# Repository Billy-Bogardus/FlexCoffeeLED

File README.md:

# FlexCoffeeLED

This Project is for the Flexible Circuit Contest by Hackaday.io
https://hackaday.io/submissions/flexible-circuit-contest/list

The Entry for this Project: https://hackaday.io/project/164555-flexible-coffee-cup-buddy
usefull links:
https://cdn.sparkfun.com/datasheets/BreakoutBoards/WS2812B.pdf

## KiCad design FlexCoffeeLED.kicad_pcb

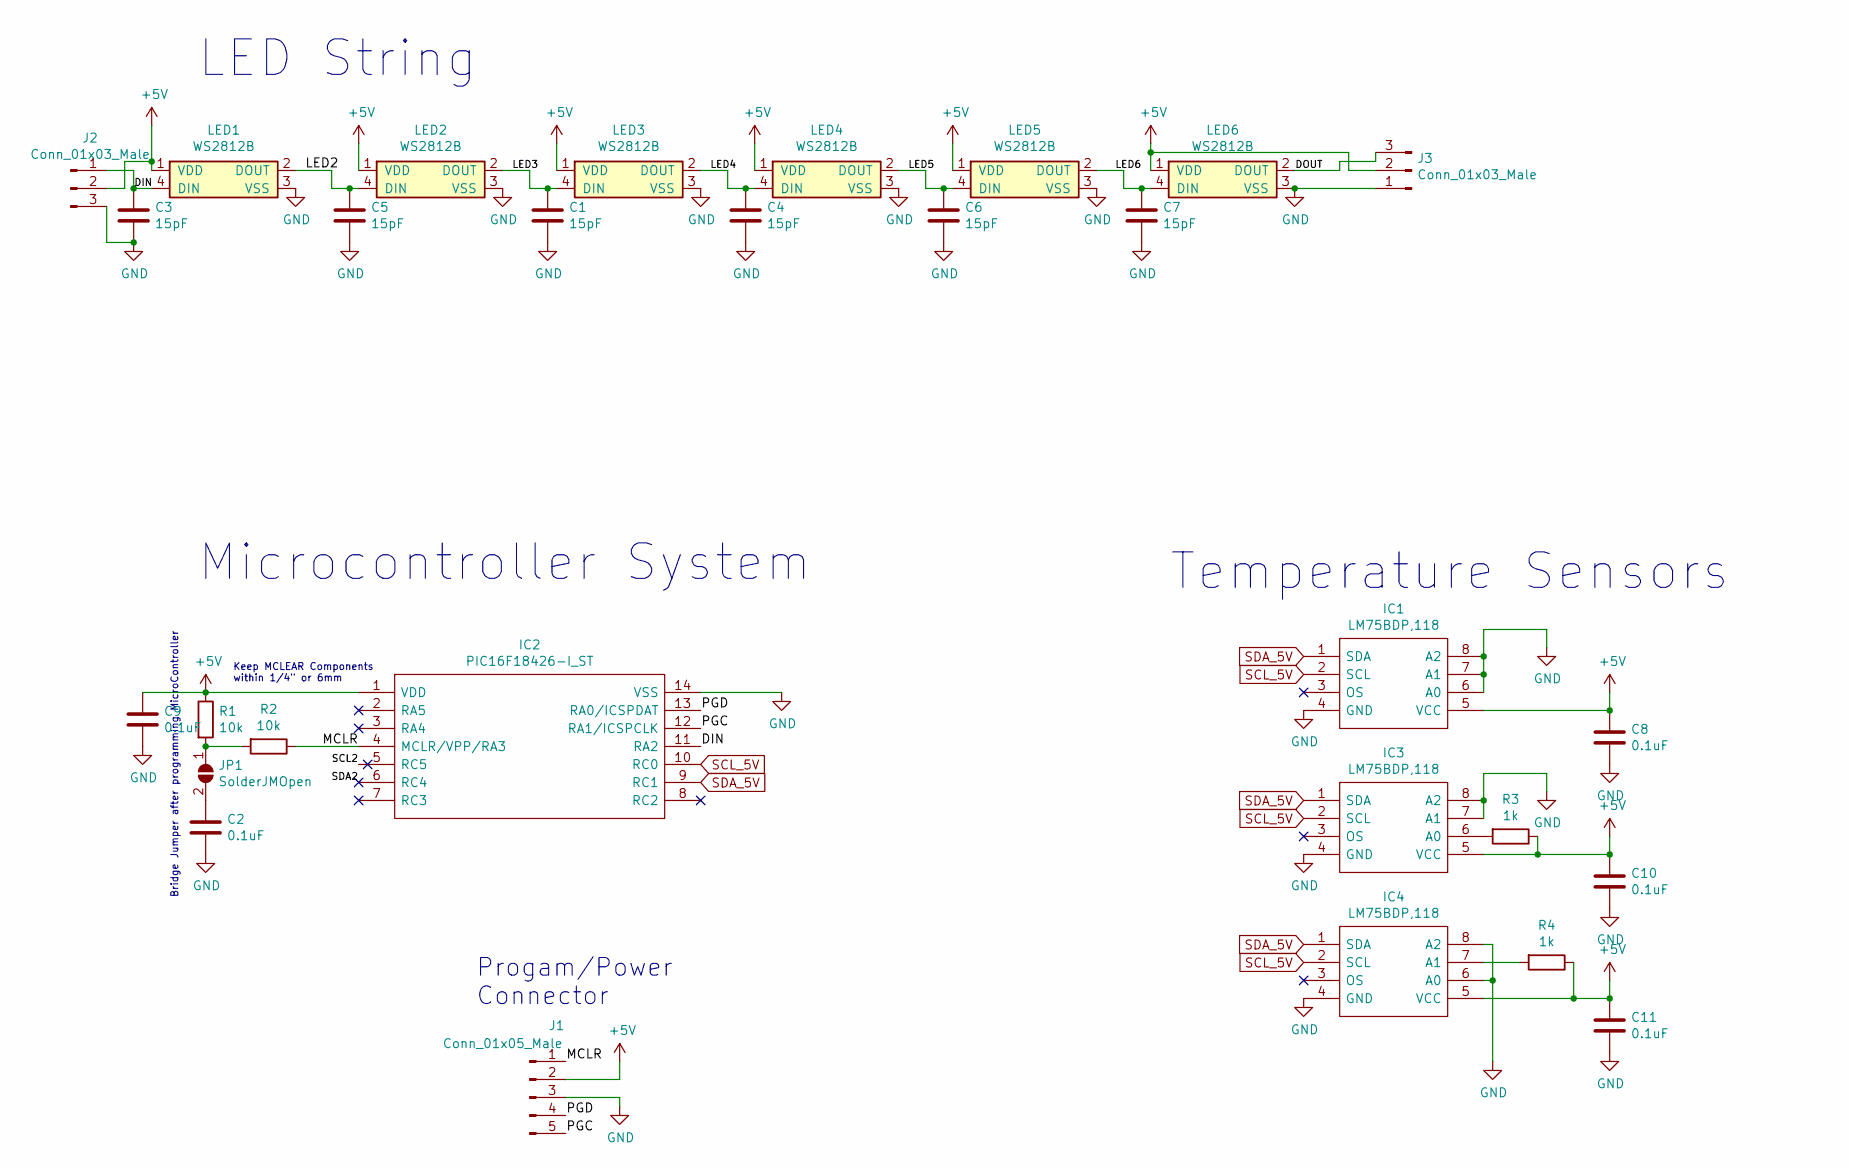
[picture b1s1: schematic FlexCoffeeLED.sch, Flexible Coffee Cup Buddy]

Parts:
C1, C3, C4, C5, C6, C7: 15pF; C_0603
C2, C8, C9, C10, C11: 0.1uF; C_0603
IC1, IC3, IC4: LM75BDP,118; SOP65P490X110-8N; Mouser Part Number 771-LM75BDP
IC2: PIC16F18426-I_ST; SOP65P640X120-14N; Manufacturer_Part_Number PIC16F18426-I/ST
J1: Conn_01x05_Male; Pin_Header_Straight_1x05_Pitch2.54mm
J2, J3: Conn_01x03_Male; Pin_Header_Straight_1x03_Pitch2.54mm
JP1: SolderJMOpen; LED_0603
LED1, LED2, LED3, LED4, LED5, LED6: WS2812B; LED_WS2812B-PLCC4
R1, R2: 10k; R_0603
R3, R4: 1k; R_0603

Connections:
+5V: C8.1, C9.1, C10.1, C11.1, IC1.5 (VCC), IC2.1 (VDD), IC3.5 (VCC), IC4.5 (VCC), J1.2, J2.2, J3.2, LED1.1 (VDD), LED2.1 (VDD), LED3.1 (VDD), LED4.1 (VDD), LED5.1 (VDD), LED6.1 (VDD), R1.1, R3.1, R4.1
/DIN: C3.1, IC2.11 (RA2), J2.1, LED1.4 (DIN)
/DOUT: J3.3, LED6.2 (DOUT)
/LED2: C5.1, LED1.2 (DOUT), LED2.4 (DIN)
/LED3: C1.1, LED2.2 (DOUT), LED3.4 (DIN)
/LED4: C4.1, LED3.2 (DOUT), LED4.4 (DIN)
/LED5: C6.1, LED4.2 (DOUT), LED5.4 (DIN)
/LED6: C7.1, LED5.2 (DOUT), LED6.4 (DIN)
/MCLR: IC2.4 (MCLR/VPP/RA3), J1.1, R2.1
/PGC: IC2.12 (RA1/ICSPCLK), J1.5
/PGD: IC2.13 (RA0/ICSPDAT), J1.4
/SCL2: IC2.5 (RC5)
/SDA2: IC2.6 (RC4)
GND: C1.2, C2.2, C3.2, C4.2, C5.2, C6.2, C7.2, C8.2, C9.2, C10.2, C11.2, IC1.4 (GND), IC1.6 (A0), IC1.7 (A1), IC1.8 (A2), IC2.14 (VSS), IC3.4 (GND), IC3.7 (A1), IC3.8 (A2), IC4.4 (GND), IC4.6 (A0), IC4.8 (A2), J1.3, J2.3, J3.1, LED1.3 (VSS), LED2.3 (VSS), LED3.3 (VSS), LED4.3 (VSS), LED5.3 (VSS), LED6.3 (VSS)
unnamed: C2.1, JP1.2 (B)
unnamed: IC3.6 (A0), R3.2
unnamed: IC4.7 (A1), R4.2
unnamed: JP1.1 (A), R1.2, R2.2
SCL_5V: IC1.2 (SCL), IC2.10 (RC0), IC3.2 (SCL), IC4.2 (SCL)
SDA_5V: IC1.1 (SDA), IC2.9 (RC1), IC3.1 (SDA), IC4.1 (SDA)

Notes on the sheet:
LED String
Microcontroller System
Progam/Power Connector
Bridge Jumper after programming MicroController
Keep MCLEAR Components within 1/4" or 6mm
Temperature Sensors

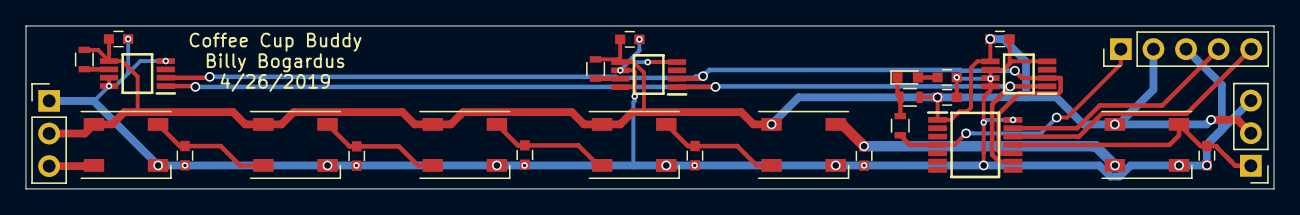
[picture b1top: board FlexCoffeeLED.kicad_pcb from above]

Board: 2 copper layers, 97.3 x 12.7 mm, 29 parts (0 on the bottom side), 18 nets.

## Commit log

2019-04-01 Starting with Clean files after experimenting with GIT.
2019-04-02 Added the major components for the project
2019-04-07 Added Data Sheets Drew Wires and added passive components and connectors
    Changes Committed:
    new file: Datasheet/MCP990_234.pdf
    new file: Datasheet/MCP990_234_AN10.14.pdf
    new file: Datasheet/MCP990_234_AN12.14.pdf
    new file: Datasheet/NCP718-D-1315705.pdf
    new file: Datasheet/Pic18F66k80.pdf
2019-04-07 Add svg diff
2019-04-07 Added Voltage Translator to I2C
2019-04-07 added no connects to up
2019-04-08 Created Board Outlines and Keepouts
2019-04-08 Just Before Renaming Q1 and Q2 Nets
2019-04-08 First Full Routing of Board
2019-04-08 DRC BUG!!!! Board looks ok
2019-04-09 3D Image
2019-04-21 add 3d View
2019-04-21 A Brand New Design
2019-04-27 Added .git attributes Routed New PCB Design Passed DRC.
2019-04-27 Second Full Board Revision
2019-04-27 small Changes
2019-05-04 Moved capacitors to proper location, and added a windmill logo
2019-05-04 updated svg
2019-08-02 Changed capacitors on LED's to 15pF
2019-08-02 Added MPLAB X IDE Folder to begin Coding.
2019-08-30 Added Code folders and Files for MPLAB
2019-10-19 Steps in coding
2019-10-21 Good code No LED Light Yet.
2019-10-21 And now we have Light!
2019-10-22 Added headder and c file for temp sense. add all white function.
2019-11-26 Minor Changes
2019-11-26 start of I2c Read
